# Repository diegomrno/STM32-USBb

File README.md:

# STM32-USBb

STM32-USBb is an **experimental PCB** based on an **STM32 microcontroller**, designed for research and prototyping purposes.

This board is part of the **Raptor project** by [Infinite](https://github.com/infiniteHQ).

> [!IMPORTANT]
> This PCB is **not production-ready**.  
> It is purely experimental and intended only for early development and future work within the Infinite project.

## Preview

## PCB

## Components list (ref & role)

- **U1** : STM32 (STM32F103C8T6) microcontroller (main MCU)
- **U2** : 3.3 V linear voltage regulator

- **Y3** : 16 MHz external crystal (MCU clock)

- **J1, J2, J3** : Pin headers (GPIO / debug / expansion)
- **J4** : USB Micro-B connector (power + USB data)

- **SW1** : Power / mode selection switch

- **D1** : Status LED

- **FB1** : Ferrite bead (power supply noise filtering)

- **R3** : USB pull-up resistor
- **R2** : MCU reset / configuration pull resistor
- **R1, R4, R5** : Current limiting / configuration resistors

- **C1, C2** : Bulk input/output decoupling capacitors
- **C3, C4, C5, C6, C11** : MCU decoupling capacitors
- **C7** : Local bulk decoupling capacitor
- **C8, C9, C10** : Power rail filtering capacitors
- **C12, C13** : Crystal load capacitors

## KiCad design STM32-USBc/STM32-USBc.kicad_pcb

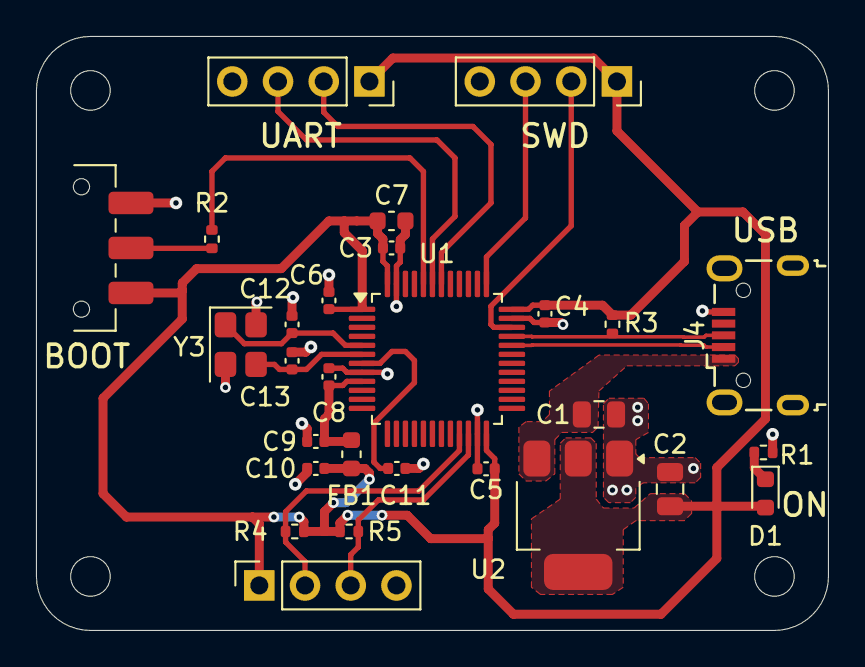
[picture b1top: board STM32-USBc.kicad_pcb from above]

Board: 2 copper layers, 44.0 x 33.0 mm, 32 parts (0 on the bottom side), 18 nets.

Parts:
C1, C2: 22u; C_0805_2012Metric
C3, C4, C5, C6, C11: 100n; C_0402_1005Metric
C7: 10u; C_0603_1608Metric
C8: 10n; C_0402_1005Metric
C9, C10: 1u; C_0402_1005Metric
C12, C13: 10p; C_0402_1005Metric
D1: LED; LED_0603_1608Metric
FB1: FerriteBead; L_0603_1608Metric
H1, H2, H3, H4: MountingHole; MountingHole_2.2mm_M2
J1, J2, J3: Conn_01x04_Pin; PinSocket_1x04_P2.54mm_Vertical
J4: USB_B_Micro; USB_Micro-B_Wuerth_629105150521
R1, R3, R4, R5: 1k5; R_0402_1005Metric
R2: 10k; R_0402_1005Metric
SW1: SW_SPDT; SW_SPDT_CK_JS102011SAQN
U1: STM32F103C8T6; LQFP-48_7x7mm_P0.5mm
U2: AMS1117-3.3; SOT-223-3_TabPin2
Y3: 16MHz; Crystal_SMD_3225-4Pin_3.2x2.5mm

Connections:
+3.3V: C2.1, C3.1, C4.1, C5.1, C6.1, C7.1, C10.1, D1.2 (A), FB1.2, J1.1, J2.1, J3.1, R3.1, R4.1, R5.1, SW1.3 (C), U1.1 (VBAT), U1.24 (VDD), U1.36 (VDD), U1.48 (VDD), U2.2 (VO)
+3.3VA: C8.1, C9.1, FB1.1, U1.9 (VDDA)
/BOOT0: R2.2, U1.44 (BOOT0)
/HSE_IN: C12.1, U1.5 (PD0), Y3.1
/HSE_OUT: C13.1, U1.6 (PD1), Y3.3
/I2C2_SCL: J3.2, R4.2, U1.21 (PB10)
/I2C2_SDA: J3.3, R5.2, U1.22 (PB11)
/NRST: C11.1, U1.7 (NRST)
/PWR_LED_K: D1.1 (K), R1.1
/SWCLK: J1.3, U1.37 (PA14)
/SWDIO: J1.2, U1.34 (PA13)
/SW_BOOT0: R2.1, SW1.2 (B)
/USART1_RX: J2.3, U1.43 (PB7)
/USART1_TX: J2.2, U1.42 (PB6)
/USB_D+: J4.3 (D+), R3.2, U1.33 (PA12)
/USB_D-: J4.2 (D-), U1.32 (PA11)
GND: C1.2, C2.2, C3.2, C4.2, C5.2, C6.2, C7.2, C8.2, C9.2, C10.2, C11.2, C12.2, C13.2, J1.4, J2.4, J3.4, J4.5 (GND), R1.2, SW1.1 (A), U1.8 (VSSA), U1.23 (VSS), U1.35 (VSS), U1.47 (VSS), U2.1 (GND), Y3.2 (G), Y3.4 (G)
VBUS: C1.1, J4.1 (VBUS), U2.3 (VI)

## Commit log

2026-02-22 add 3d model for USB c receptacle
2026-02-22 pre rooting
2026-02-22 3d model of switch + layout borders
2026-02-22 switch to usb b
2026-02-22 final rooting and texts
2026-02-22 readme and position file
2026-02-22 fix readme
